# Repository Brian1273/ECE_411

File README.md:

# ECE_411

ECE411 practicum project:  Metronome.

Objectives:

Use an input device such as a sensor
Use an output device such as an LED or sound emitter
Use a microcontroller to manager the signals.

All of these items are combined to create a metronome that is capable of pace setting and provides visual and auditory feedback.

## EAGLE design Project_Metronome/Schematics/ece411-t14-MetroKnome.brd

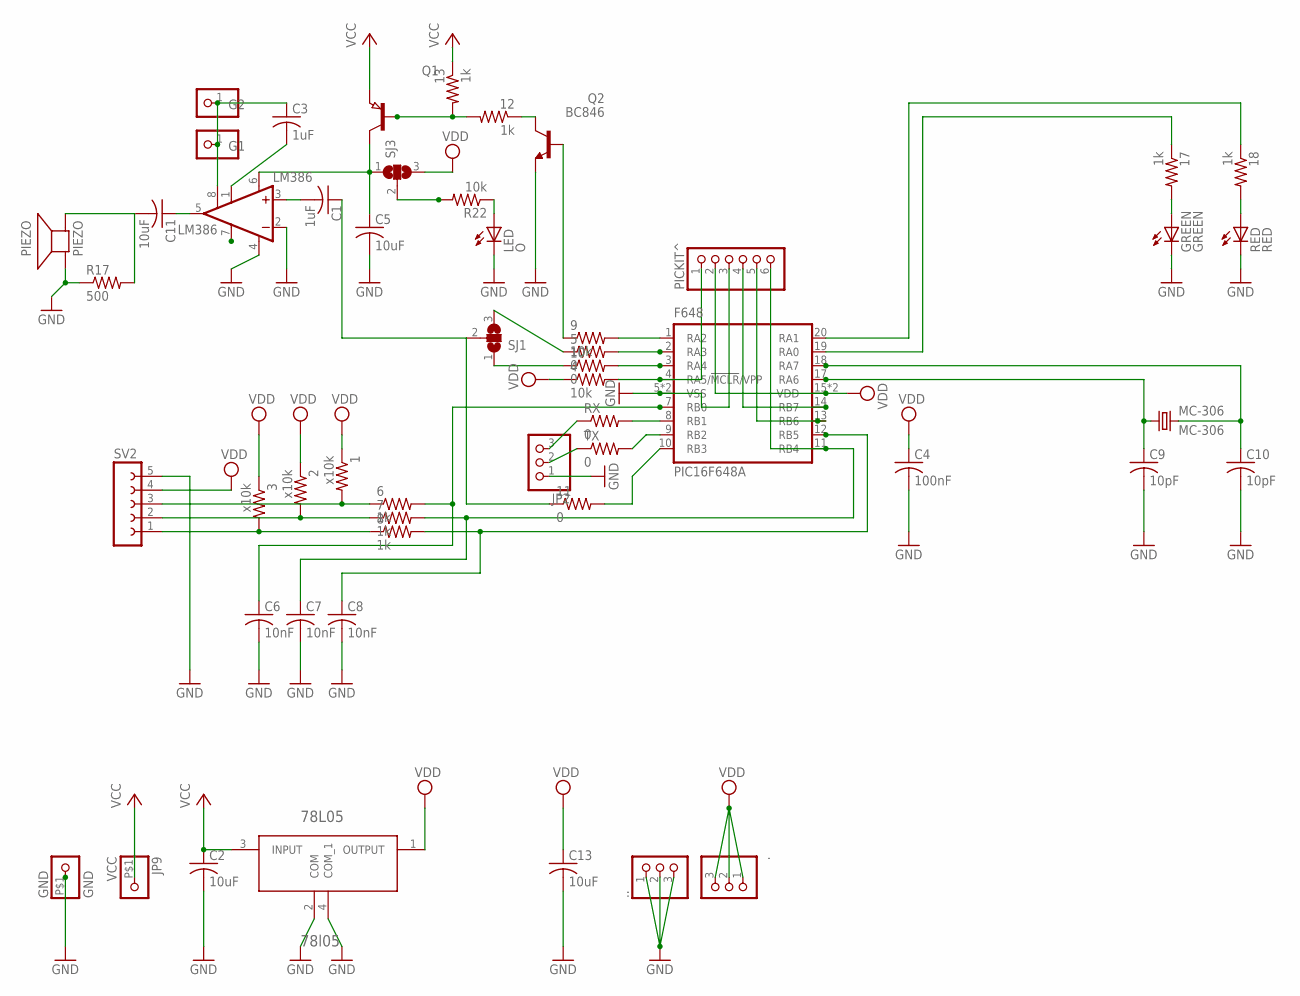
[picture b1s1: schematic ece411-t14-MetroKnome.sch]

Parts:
1, 2, 3: x10k; R1206
4, 9: 10k; R1206
5, 10: 0; R0603
6, 7, 8, 12, 13, 17, 18: 1k; R1206
11: 0; R1206
78L05: 78l05; SOT150P400X160-4N
., ..: PINHD-1X3CB; 1X03-CLEANBIG
C1, C3: 1uF; C1210
C2, C5, C11, C13: 10uF; C1210
C4: 100nF; C1210
C6, C7, C8: 10nF; C1210
C9, C10: 10pF; C1210
F648: PIC16F648A; SSOP20
G1, G2: PINHD-1X1CB; 1X01-CLEANBIG
GND: GND; 1X1-BIGPOGO
GREEN: GREEN; LED5MM
JP2: PINHD-1X3CB; 1X03-CLEANBIG
JP9: VCC; 1X1-BIGPOGO
LED: O; CHIPLED_1206
LM386: LM386; SO08
MC-306: MC-306; MPN MC-306 60.0KHZ 100PPM ,12.5PF
PICKIT^: PINHD-1X6LOCK; 1X06-BIGLOCK
PIEZO: PIEZO; AL60P
Q1: PNP-TRANSISTOR_SOT89; SOT89
Q2: BC846; SOT23
R17: 500; R1206
R22: 10k; R1206
RED: RED; LED5MM
RX: 0; R1206
SJ1, SJ3: SJ2W; SJ_2
SV2: FE05-1
TX: 0; R1206

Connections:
GND: 78L05.2 (COM), 78L05.4 (COM_1), ...1, ...2, ...3, C2.2, C4.2, C5.2, C6.2, C7.2, C8.2, C9.2, C10.2, C13.2, F648.5 (VSS), F648.6 (VSS), GND.P$1, GREEN.K (C), JP2.1, LED.C, LM386.2 (-IN), LM386.4 (GND), PICKIT^.3, PIEZO.2 (-), Q2.2 (E), R17.1, RED.K (C), SV2.5
unnamed: 9.2, F648.1 (RA2)
unnamed: C3.2, LM386.1 (GAIN)
unnamed: 9.1, Q2.1 (B)
unnamed: 5.2, F648.2 (RA3)
unnamed: 4.2, F648.4 (RA5/!MCLR!/VPP), PICKIT^.1
unnamed: 6.2, C6.1, F648.7 (RB0)
unnamed: JP2.3, RX.1
unnamed: 8.2, C8.1, F648.12 (RB5)
unnamed: 10.2, F648.3 (RA4)
unnamed: 11.2, F648.10 (RB3)
unnamed: 12.1, Q2.3 (C)
unnamed: 12.2, 13.2, Q1.1 (B)
unnamed: C3.1, G1.1, G2.1, LM386.8 (GAIN)
unnamed: 1.2, 6.1, SV2.3
unnamed: 2.2, 7.1, SV2.2
unnamed: 3.2, 8.1, SV2.1
unnamed: JP2.2, TX.1
unnamed: 17.1, F648.19 (RA0)
unnamed: 18.1, F648.20 (RA1)
unnamed: 7.2, C7.1, F648.11 (RB4), PICKIT^.6
unnamed: F648.9 (RB2), TX.2
unnamed: F648.14 (RB7), PICKIT^.4
unnamed: F648.8 (RB1), RX.2
unnamed: F648.13 (RB6), PICKIT^.5
unnamed: R22.2, SJ3.2
unnamed: 10.1, SJ1.1
unnamed: 18.2, RED.A
unnamed: 17.2, GREEN.A
unnamed: 5.1, SJ1.3
unnamed: C9.1, F648.17 (RA6), MC-306.1
unnamed: C1.2, LM386.3 (+IN)
unnamed: C11.1, LM386.5 (OUT)
unnamed: C10.1, F648.18 (RA7), MC-306.4 (2)
unnamed: C11.2, PIEZO.1 (+), R17.2
unnamed: LED.A, R22.1
unnamed: 11.1, C1.1, SJ1.2
VCC: 13.1, 78L05.3 (INPUT), C2.1, JP9.P$1, Q1.3 (E)
VDD: 1.1, 2.1, 3.1, 4.1, 78L05.1 (OUTPUT), ..1, ..2, ..3, C4.1, C13.1, F648.15 (VDD), F648.16 (VDD), PICKIT^.2, SJ3.3, SV2.4
VS: C5.1, LM386.6 (VS), Q1.2 (C), SJ3.1

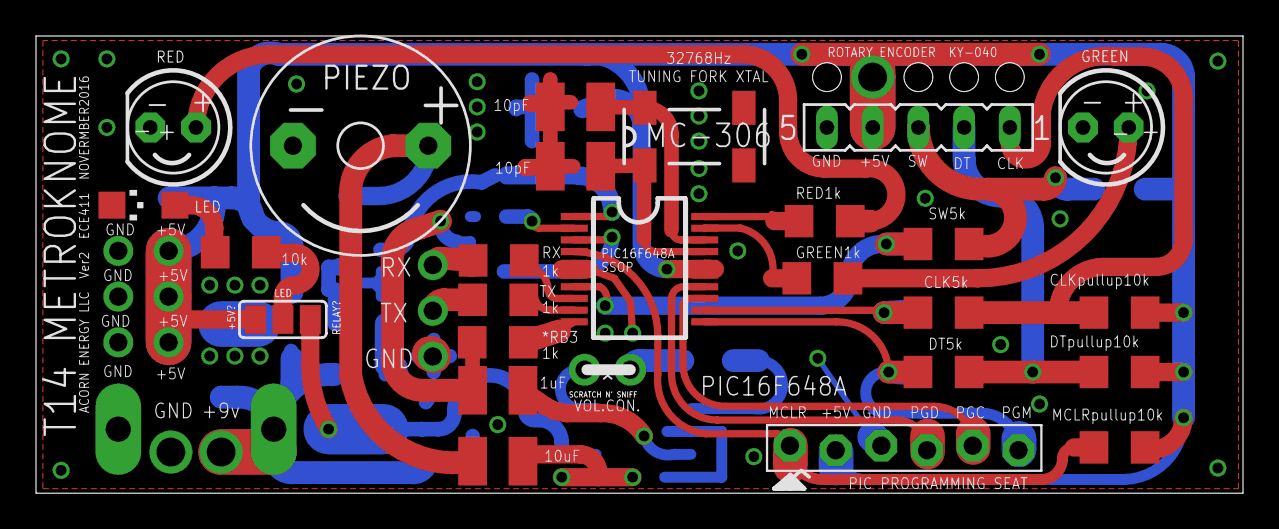
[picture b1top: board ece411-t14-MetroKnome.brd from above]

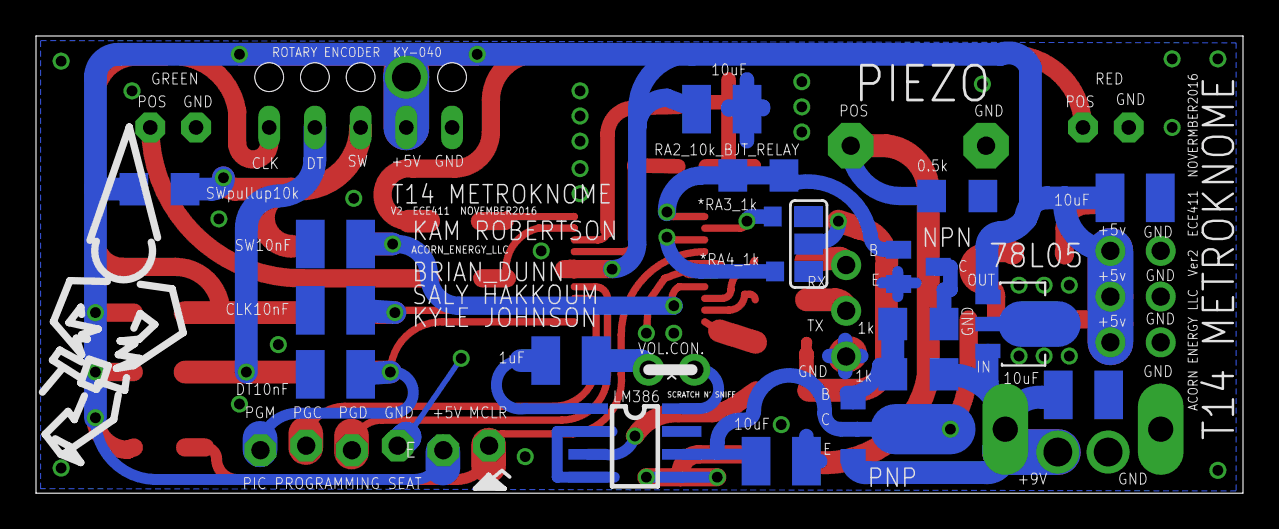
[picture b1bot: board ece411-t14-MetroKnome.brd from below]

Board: 2 copper layers, 67.1 x 25.4 mm, 52 parts (24 on the bottom side), 40 nets.

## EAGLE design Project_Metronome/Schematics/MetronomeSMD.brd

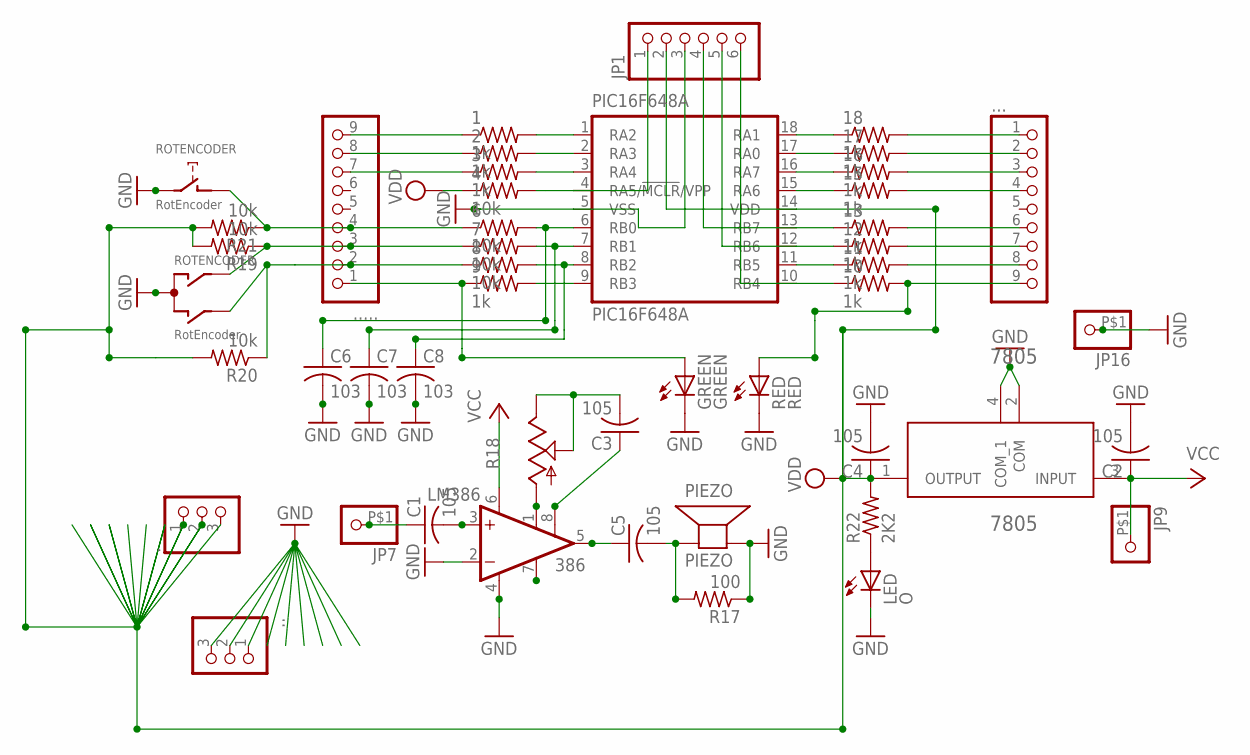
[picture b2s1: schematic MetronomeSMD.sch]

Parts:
1, 2, 3, 9, 10, 11, 12, 13, 15, 16, 17, 18: 1k; R1206
4, 6, 7, 8: 10k; R1206
7805: 7805; SOT150P400X160-4N
., ..: PINHD-1X3CB; 1X03-CLEANBIG
..., .....: PINHD-1X9; 1X09-BIG
C1, C2, C3, C4, C5: 105; C1210
C6, C7, C8: 103; C1210
GREEN: GREEN; LED5MM
JP1: PINHD-1X6LOCK; 1X06-BIGLOCK
JP7, JP9, JP16: PINHD-1X1-BIGPOGO; 1X1-BIGPOGO
LED: O; CHIPLED_1206
LM386: 386; SO08
PIC16F648A: PIC16F648A; DIL18
PIEZO: PIEZO; PS12
R17: 100; R1206
R18: TRIM_US-RJ9W; RJ9W
R19, R20, R21: 10k; R1206
R22: 2K2; R1206
RED: RED; LED5MM
ROTENCODER: RotEncoder; ALPS_EC12E_SW

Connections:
GND: 7805.2 (COM), 7805.4 (COM_1), ...1, ...2, ...3, C2.2, C4.2, C6.2, C7.2, C8.2, GREEN.K (C), JP1.3, JP16.P$1, LED.C, LM386.2 (-IN), LM386.4 (GND), PIC16F648A.5 (VSS), PIEZO.P$2 (-), R17.1, RED.K (C), ROTENCODER.C, ROTENCODER.E (2)
unnamed: 9.2, PIC16F648A.9 (RB3)
unnamed: 1.2, PIC16F648A.1 (RA2)
unnamed: 2.2, PIC16F648A.2 (RA3)
unnamed: 3.2, PIC16F648A.3 (RA4)
unnamed: 4.2, JP1.1, PIC16F648A.4 (RA5/!MCLR!/VPP)
unnamed: 6.2, C6.1, PIC16F648A.6 (RB0)
unnamed: 7.2, C7.1, PIC16F648A.7 (RB1)
unnamed: 8.2, C8.1, PIC16F648A.8 (RB2)
unnamed: 1.1, ......9
unnamed: 2.1, ......8
unnamed: 3.1, ......7
unnamed: 6.1, ......4, R21.1, ROTENCODER.D (1)
unnamed: 7.1, ......3, R19.1, ROTENCODER.A
unnamed: 8.1, ......2, R20.1, ROTENCODER.B
unnamed: 9.1, ......1, GREEN.A
unnamed: 18.1, PIC16F648A.18 (RA1)
unnamed: 17.1, PIC16F648A.17 (RA0)
unnamed: 16.1, PIC16F648A.16 (RA7)
unnamed: 15.1, PIC16F648A.15 (RA6)
unnamed: 13.1, JP1.4, PIC16F648A.13 (RB7)
unnamed: C3.1, LM386.8 (GAIN)
unnamed: 12.1, JP1.5, PIC16F648A.12 (RB6)
unnamed: LM386.1 (GAIN), R18.A
unnamed: 11.1, PIC16F648A.11 (RB5)
unnamed: 10.1, JP1.6, PIC16F648A.10 (RB4)
unnamed: 18.2, ....1
unnamed: 17.2, ....2
unnamed: 16.2, ....3
unnamed: 15.2, ....4
unnamed: 13.2, ....6
unnamed: C3.2, R18.E, R18.S
unnamed: 12.2, ....7
unnamed: C1.2, LM386.3 (+IN)
unnamed: C5.1, LM386.5 (OUT)
unnamed: 11.2, ....8
unnamed: 10.2, ....9, RED.A
unnamed: C5.2, PIEZO.P$1 (+), R17.2
unnamed: LED.A, R22.1
unnamed: C1.1, JP7.P$1
VCC: 7805.3 (INPUT), C2.1, JP9.P$1, LM386.6 (VS)
VDD: 4.1, 7805.1 (OUTPUT), ..1, ..2, ..3, C4.1, JP1.2, PIC16F648A.14 (VDD), R19.2, R20.2, R21.2, R22.2

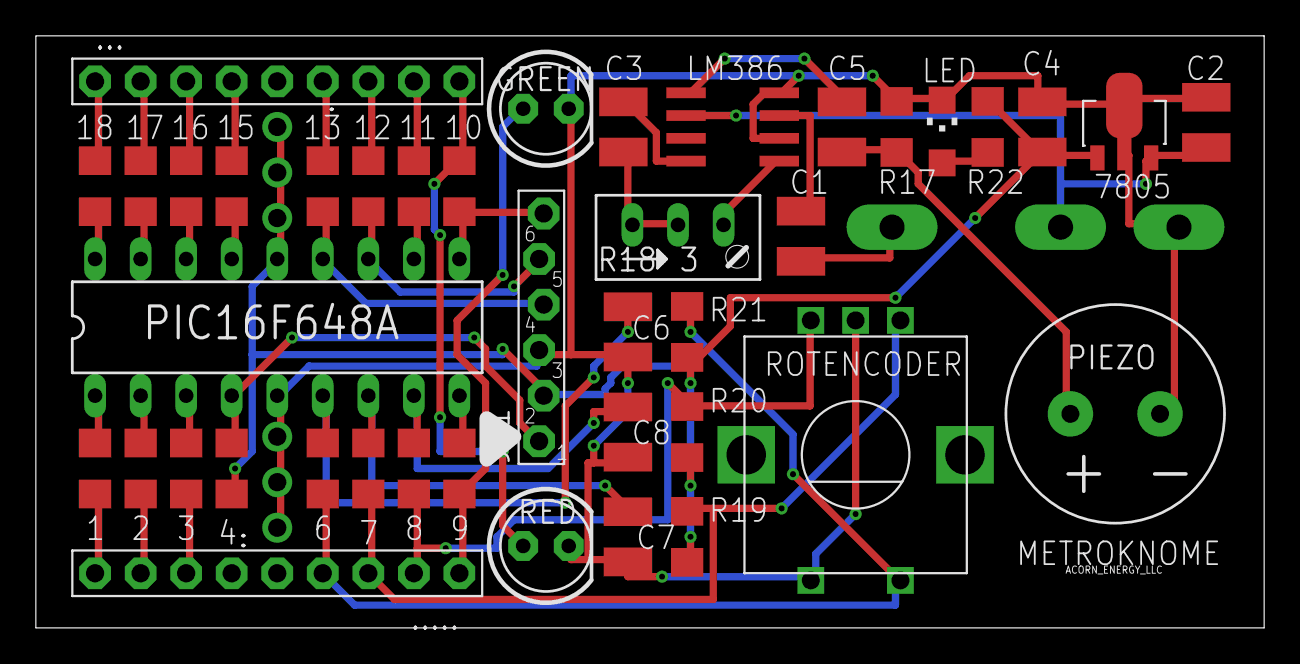
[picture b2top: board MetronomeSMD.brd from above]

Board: 2 copper layers, 68.5 x 33.0 mm, 46 parts (0 on the bottom side), 42 nets.

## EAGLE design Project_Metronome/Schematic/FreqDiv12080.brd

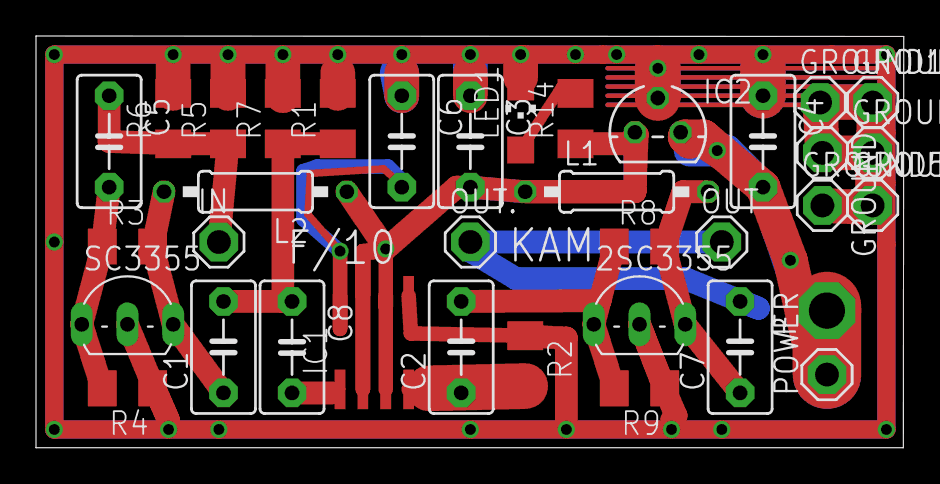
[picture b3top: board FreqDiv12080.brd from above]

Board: 2 copper layers, 48.2 x 22.9 mm, 36 parts (0 on the bottom side), 14 nets.

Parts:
2SC3355: TO92-BEC
C1, C2, C5, C6, C7, C8: 1nF; C5B3.5
C3, C4: 1uF; C5B3.5
GROUND, GROUND1, GROUND2, GROUND3, GROUND4, GROUND5: SE13
IC1: MC12080D; SO08
IC2: 78L05Z; TO92
IN: SE13
L1, L2: 1mH; 0207/10
LED1: CHIPLED_1206
OUT, OUT.: SE13
P: TPPAD1-20; P1-20
POWER: SE13
R1, R5, R6, R7: 100; M1206
R2: 820; M1206
R3, R8: 10k; M1206
R4, R9: 3k3; M1206
R14: 1k; M1206
SC3355: TO92-BEC

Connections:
unnamed: C4.2, IC2.3, P.TP, POWER.MP
unnamed: C2.1, IC1.4, R2.2
unnamed: 2SC3355.B, C2.2, R8.1, R9.2
unnamed: C3.2, IC1.2, IC1.3, IC1.6, IC1.7, IC2.1, L1.1, L2.1, R14.1
unnamed: C5.1, IN.MP, R5.1, R6.1
unnamed: C5.2, R3.1, R4.2, SC3355.B
unnamed: C7.2, OUT.MP, OUT..MP
unnamed: 2SC3355.C, C7.1, L1.2, R8.2
unnamed: LED1.A, R14.2
unnamed: C6.2, IC1.8
unnamed: C1.2, C8.1, R1.1, R7.1
unnamed: 2SC3355.E, C3.1, C4.1, C6.1, GROUND.MP, GROUND1.MP, GROUND2.MP, GROUND3.MP, GROUND4.MP, GROUND5.MP, IC1.5, IC2.2, LED1.C, R1.2, R2.1, R4.1, R5.2, R6.2, R7.2, R9.1, SC3355.E
unnamed: C8.2, IC1.1
unnamed: C1.1, L2.2, R3.2, SC3355.C

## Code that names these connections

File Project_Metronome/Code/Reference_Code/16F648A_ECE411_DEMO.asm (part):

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; PROGRAM FUNCTION:	METROKNOME 
;					want: alternate flashing two led's
;					want: sound a piezo buzzer with each flash of an led
;					have: toggle output using the interrupt at pin RB0/INT
;					want: control speed with RB1 and RB2 by polling at interrupt
;********************************************************************************
; NOTES:			have: flash 5volts to RA3,RA2,RA1,RA0,RB5,RB3
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	CALL initializer	; CALL the function "initializer"
	goto main
main
	BSF PORTA, 4	; SOURCE LED at pin RA4, use bit-number for bit-position(3,2,1,0)
	MOVLW d1		; moves literal number into working register passing this literal to the function delay
	CALL delay		; CALL the function "delay"
	BCF PORTA, 4 	; SINK LED at pin RA4 (3,2,1,0 bit position)
	MOVLW d1		; moves literal into register "w".  use "w" to pass number of loops thru to function "delay"
	CALL delay		; CALL the function "delay"
	;
	BSF porta, 4	; SOURCE LED at pin RA4, use bit-number for bit-position(3,2,1,0)
	MOVLW d2		; moves literal number into working register passing this literal to the function delay
	CALL delay		; CALL the function "delay"
	BCF porta, 4 	; SINK LED at pin RA4 (3,2,1,0 bit position)
	MOVLW d2		; moves literal into register "w".  use "w" to pass number of loops thru to function "delay"
	CALL delay		; CALL the function "delay"
	;
	BSF porta, 4	; SOURCE LED at pin RA4, use bit-number for bit-position(3,2,1,0)
	MOVLW d3		; moves literal number into working register passing this literal to the function delay
	CALL delay		; CALL the function "delay"
	BCF porta, 4 	; SINK LED at pin RA4 (3,2,1,0 bit position)
	MOVLW d3		; moves literal into register "w".  use "w" to pass number of loops thru to function "delay"
	CALL delay		; CALL the function "delay"
	;
	;
	;
	BSF PORTA, 3	; SOURCE LED at pin RA3, use bit-number for bit-position(3,2,1,0)
	MOVLW d1		; moves literal number into working register passing this literal to the function delay
	CALL delay		; CALL the function "delay"
	BCF PORTA, 3 	; SINK LED at pin RA3 (3,2,1,0 bit position)
	MOVLW d1		; moves literal into register "w".  use "w" to pass number of loops thru to function "delay"
	CALL delay		; CALL the function "delay"
	;
	BSF porta, 3	; SOURCE LED at pin RA3, use bit-number for bit-position(3,2,1,0)
	MOVLW d2		; moves literal number into working register passing this literal to the function delay
	CALL delay		; CALL the function "delay"
	BCF porta, 3 	; SINK LED at pin RA3 (3,2,1,0 bit position)
	MOVLW d2		; moves literal into register "w".  use "w" to pass number of loops thru to function "delay"
	CALL delay		; CALL the function "delay"
	;
	BSF porta, 3	; SOURCE LED at pin RA3, use bit-number for bit-position(3,2,1,0)
	MOVLW d3		; moves literal number into working register passing this literal to the function delay
	CALL delay		; CALL the function "delay"
	BCF porta, 3 	; SINK LED at pin RA3 (3,2,1,0 bit position)
	MOVLW d3		; moves literal into register "w".  use "w" to pass number of loops thru to function "delay"
	CALL delay		; CALL the function "delay"
	;
	;
	;	
	BSF PORTA, 2	; SOURCE LED at pin RA2, use bit-number for bit-position(3,2,1,0)
	MOVLW d1		; moves literal number into working register passing this literal to the function delay
	CALL delay		; CALL the function "delay"
	BCF PORTA, 2 	; SINK LED at pin RA2 (3,2,1,0 bit position)
	MOVLW d1		; moves literal into register "w".  use "w" to pass number of loops thru to function "delay"
	CALL delay		; CALL the function "delay"
	;
	BSF porta, 2	; SOURCE on LED at pin RA2, use bit-number for bit-position(3,2,1,0)
	MOVLW d2		; moves literal number into working register passing this literal to the function delay
	CALL delay		; CALL the function "delay"
	BCF porta, 2 	; SINK LED at pin RA2 (3,2,1,0 bit position)
	MOVLW d2		; moves literal into register "w".  use "w" to pass number of loops thru to function "delay"
	CALL delay		; CALL the function "delay"
	;
	BSF porta, 2	; SOURCE LED at pin RA2, use bit-number for bit-position(3,2,1,0)
	MOVLW d3		; moves literal number into working register passing this literal to the function delay
	CALL delay		; CALL the function "delay"
	BCF porta, 2 	; SINK off LED at pin RA2 (3,2,1,0 bit position)
	MOVLW d3		; moves literal into register "w".  use "w" to pass number of loops thru to function "delay"
	CALL delay		; CALL the function "delay"
	;
	;
	;
	BSF PORTA, 1	; SOURCE LED at pin RA1, use bit-number for bit-position(3,2,1,0)
	MOVLW d1		; moves literal number into working register passing this literal to the function delay
	CALL delay		; CALL the function "delay"
	BCF PORTA, 1 	; SINK LED at pin RA1 (3,2,1,0 bit position)
	MOVLW d1		; moves literal into register "w".  use "w" to pass number of loops thru to function "delay"
	CALL delay		; CALL the function "delay"
	;
	BSF porta, 1	; SOURCE LED at pin RA1, use bit-number for bit-position(3,2,1,0)
	MOVLW d2		; moves literal number into working register passing this literal to the function delay
	CALL delay		; CALL the function "delay"
	BCF porta, 1 	; SINK LED at pin RA1 (3,2,1,0 bit position)
	MOVLW d2		; moves literal into register "w".  use "w" to pass number of loops thru to function "delay"
	CALL delay		; CALL the function "delay"
	;
	BSF porta, 1	; SOURCE LED at pin RA1, use bit-number for bit-position(3,2,1,0)
	MOVLW d3		; moves literal number into working register passing this literal to the function delay
	CALL delay		; CALL the function "delay"
	BCF porta, 1 	; SINK LED at pin RA1 (3,2,1,0 bit position)
	MOVLW d3		; moves literal into register "w".  use "w" to pass number of loops thru to function "delay"
	CALL delay		; CALL the function "delay"
	;
	;
	;	
	BSF PORTA, 0	; SOURCE LED at pin RA0, use bit-number for bit-position(3,2,1,0)
	MOVLW d1		; moves literal number into working register passing this literal to the function delay
	CALL delay		; CALL the function "delay"
	BCF PORTA, 0 	; SINK LED at pin RA0 (3,2,1,0 bit position)
	MOVLW d1		; moves literal into register "w".  use "w" to pass number of loops thru to function "delay"
	CALL delay		; CALL the function "delay"
	;
	BSF porta, 0	; SOURCE LED at pin RA0, use bit-number for bit-position(3,2,1,0)
	MOVLW d2		; moves literal number into working register passing this literal to the function delay
	CALL delay		; CALL the function "delay"
	BCF porta, 0 	; SINK LED at pin RA0 (3,2,1,0 bit position)
	MOVLW d2		; moves literal into register "w".  use "w" to pass number of loops thru to function "delay"
	CALL delay		; CALL the function "delay"
	;
	BSF porta, 0	; SOURCE LED at pin RA0, use bit-number for bit-position(3,2,1,0)
	MOVLW d3		; moves literal number into working register passing this literal to the function delay
	CALL delay		; CALL the function "delay"
	BCF porta, 0 	; SINK LED at pin RA0 (3,2,1,0 bit position)
	MOVLW d3		; moves literal into register "w".  use "w" to pass number of loops thru to function "delay"
	CALL delay		; CALL the function "delay"
	;
	;
	;
;	BSF PORTA, 7	; turn on LED at pin RA7, use bit-number for bit-position(3,2,1,0)
;	MOVLW d1		; moves literal number into working register passing this literal to the function delay
;	CALL delay	; CALL the function "delay"
;	BCF PORTA, 7 	; turn off LED at pin RA7 (3,2,1,0 bit position)
;	MOVLW d1		; moves literal into register "w".  use "w" to pass number of loops thru to function "delay"
;	CALL delay	; CALL the function "delay"
;	;
;	BSF porta, 7	; turn on LED at pin RA7, use bit-number for bit-position(3,2,1,0)
;	MOVLW d2		; moves literal number into working register passing this literal to the function delay
;	CALL delay	; CALL the function "delay"
;	BCF porta, 7 	; turn off LED at pin RA7 (3,2,1,0 bit position)
;	MOVLW d2			; moves literal into register "w".  use "w" to pass number of loops thru to function "delay"
;	CALL delay	; CALL the function "delay"
;	;
;	BSF porta, 7	; turn on LED at pin RA7, use bit-number for bit-position(3,2,1,0)
;	MOVLW d3		; moves literal number into working register passing this literal to the function delay
;	CALL delay	; CALL the function "delay"
;	BCF porta, 7 	; turn off LED at pin RA7 (3,2,1,0 bit position)
;	MOVLW d3			; moves literal into register "w".  use "w" to pass number of loops thru to function "delay"
;	CALL delay	; CALL the function "delay"
;	;
;	;
;	;	
;	BSF PORTA, 6	; turn on LED at pin RA6, use bit-number for bit-position(3,2,1,0)
;	MOVLW d1		; moves literal number into working register passing this literal to the function delay
;	CALL delay	; CALL the function "delay"
;	BCF PORTA, 6 	; turn off LED at pin RA6 (3,2,1,0 bit position)
;	MOVLW d1		; moves literal into register "w".  use "w" to pass number of loops thru to function "delay"
;	CALL delay	; CALL the function "delay"
;	;
;	BSF porta, 6	; turn on LED at pin RA6, use bit-number for bit-position(3,2,1,0)
;	MOVLW d2		; moves literal number into working register passing this literal to the function delay
;	CALL delay	; CALL the function "delay"
;	BCF porta, 6 	; turn off LED at pin RA6 (3,2,1,0 bit position)
;	MOVLW d2			; moves literal into register "w".  use "w" to pass number of loops thru to function "delay"
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
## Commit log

2016-10-02 Component pdf
    Component pdf
2016-10-04 PROJECT IDEA
2016-10-05 DEV_BOARD_LTSPICE
2016-10-05 INITIAL_SOFTWARE
2016-10-06 INITIAL_DATA
2016-10-06 ReferenceCode
2016-10-06 ECE11_Homework_2
2016-10-06 Add files via upload
    Homework 2 first draft
2016-10-06 Add files via upload
    Added projects ideas
2016-10-06 Gantt Chart
    GanttProject option
2016-10-07 PDF version of Gantt chart
    Preliminary schedule (work in progress), PDF version for now to get an idea of what it would look like.
2016-10-07 Add files via upload
    Added / Compiled ideas for project.
2016-10-11 Initial_Parts_List
    first pass look at base parts needed (this is a working/growing list)
2016-10-11 October_13_Project_Meeting
    Team meeting to review project status, assign action items, development
2016-10-11 Create Project_Archives
2016-10-11 Repository for Archives
2016-10-11 Project Proposal
    From our google docs to get into version control system
2016-10-11 Project_Metronome
    Location for metronome project
2016-10-12 FAB SHOP
    EagleCAD diagram and schematic submitted as a test board to OshPark
    I expect the pcb's by 24OCT2016
2016-10-12 Dev. Board Components
2016-10-12 Rotary encoder
    I am working on setting one of these up for use on the dev board.
    The knob push button will operate the interrupt pin
    The rotating knob uses two pins to control slower/faster in digital increments
2016-10-12 FUN PICTURES
    rough proto circuit.... no enclosure dimensions, likely spelling errors, pins not declared---- except for the rotary encoder, those are good pins.
    The pictures are from OshPark showing what our PCB could look like for evaluation.
2016-10-12 better eagle files
2016-10-12 better eagle files
    the traces are auto trash and there is a lot of "extra parts", but the form is coming together. Width is close to the size of enclosures I am investigating. The short dimension can still be shrunk fu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
2016-10-13 Datasheets
    Place datasheets here
2016-10-13 Parts List
2016-10-13 Schematics
    placeholder for schematics
2016-10-13 Code
    Placeholder for code
2016-10-13 Assy & Debug
    empty file placeholder
2016-10-13 Documentation
    empty file placeholder
2016-10-13 Rename Project_Metronome/FreqDiv12080.brd to Project_Metronome/Schematic/FreqDiv12080.brd
    Moved to Schematic folder
2016-10-13 Rename Project_Metronome/Schematic/FreqDiv12080.brd to Project_Metronome/Schematics/FreqDiv12080.brd
2016-10-13 Rename Project_Metronome/FreqDiv12080.sch to Project_Metronome/Schematics/FreqDiv12080.sch
2016-10-13 Rename Parts_List/PARTS_SHEET.txt to Project_Metronome/Parts_List/PARTS_SHEET.txt
2016-10-13 Rename Parts_List/Initial_Parts_List to Project_Metronome/Parts_List/Initial_Parts_List
2016-10-13 Rename Fan_Controller_Idea.txt to Archives/Fan_Controller_Idea.txt
2016-10-13 Rename Holiday_Controller_Idea.txt to Archives/Holiday_Controller_Idea.txt
2016-10-13 Rename Holiday_Ornament_Idea.txt to Archives/Holiday_Ornament_Idea.txt
2016-10-13 Rename Tuning_Fork_Idea.txt to Project_Metronome/Schematics/Tuning_Fork_Idea.txt
2016-10-13 Oct 13 Project Meeting
2016-10-13 MPLAB_version_8.92
    http://www.microchip.com/development-tools/downloads-archive
2016-10-13 MPLAB_version_8.92 IDE
    http://www.microchip.com/development-tools/downloads-archive
2016-10-14 Corrected names and pull up added to MCLR
2016-10-15 Rename METRONOME_INITIAL_DATA.txt to Project_Metronome/METRONOME_INITIAL_DATA.txt
2016-10-16 Create Dropbox
2016-10-16 Schematic
2016-10-20 code demo
2016-10-25 PDS_Oct_24_2016
2016-10-31 BOM snd COST
2016-11-03 Board and Diagram
    v4MetroKnome submitted to OshPark
    v4_1MetroKnome is nearing completion for 17NOV16 submittal
2016-11-03 Pictures of Rev.1 submitted to Oshpark 28OCT16
2016-11-03 Rev.1 OshPark Reciept
2016-11-07 Homework_4_msproject
    Initial draft of Homework_4, microsoft project. Need to add software related steps from layout to demonstration.
2016-11-07 Current PCB
    board and diagram with oshpark generated pictures
2016-11-09 Homework_04_Project_Schedule_02
    MS_Project, second revision to initial draft
2016-11-13 FINISHED PCB
    FAB SHOP ON THE 17th
2016-11-18 Vaccine system monitoring HW#5
2016-11-20 Current cost estimate and bom
    $
2016-11-23 Add files via upload
    Test program to test encoder funtionality
2016-11-23 Add files via upload
    Test script for rotary encoder, Lights will indicate state of encoder output. Push button goes to interrupt procedure which will indicate an increment or decrement from encoder.
2016-11-23 Add files via upload
    MetroKnome Program Flow Chart
2016-11-24 Homework_6 Test Plan
    Homework_6 Test Plan
2016-11-24 archives
    saving previous versions or drafts
2016-11-30 PWM code
2016-12-01 Project Progression
    evolution of design from proto to final solution
2016-12-01 placeholder
    evolution of design from proto to final solution
2016-12-01 Block Diagram
    initial concept block diagram
2016-12-01 Proto_01
    Initial prototype board
2016-12-01 Proto_02
2016-12-01 Pre-final_solution
2016-12-01 final_solution_02_top_view
    top view of finished product in case
2016-12-01 final_solution_03
    top view with case cover removed
2016-12-01 final_solution_01
    front view of final solution
2016-12-01 tools
2016-12-01 test and debug
    test and debug of final solution (prior to casing)
2016-12-04 Moved files to new directory
2016-12-04 Moved file to new location
2016-12-04 Moved 101_9720.jpg to images folder
2016-12-04 Example reference code
2016-12-04 moved refernce code to new folder
2016-12-04 moved decision matrix to homework folder
2016-12-04 LTspice schematic capture
    During development phase of design (Oct 2016)
2016-12-04 moved LTspice schematic to appropriate directory
2016-12-04 Create T14_MetroKnome_beta_V1.0
    First working Configuration
2016-12-05 Add files via upload
    Final version. Fixed linearity with encoder rate tic_rate was adjusted to slightly less than 10ms.
2016-12-05 Update T14_MetroKnome_FINAL_v1.0.asm
    Comments fixes
2016-12-07 board layout image
2016-12-07 github notes (renaming files)
2016-12-08 Update to test plan
    added test_cases to verify functionality of rotary encoder
2016-12-08 Fixed table of contents in test plan document
    updated table of contents in test plan document
2016-12-08 Project Presentation
    Latest and greatest (-08 from google drive)
2016-12-08 PWM mode initial notes
2016-12-08 Another version of final presentation
2016-12-08 Another approach of T14_Metronome code
2016-12-08 Homework_06_rev_04
    Updates to test_plan (additional test_cases)
2016-12-08 Presentation Updated
    Latest presentation upload
2016-12-08 Presentation Update
